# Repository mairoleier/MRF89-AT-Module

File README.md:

# MRF_AT_868/915_v1.0

This is  the first version of MRF89XA 868MHz RF module that could be controlled with AT commands. 
It has integrated MSP430FR5969 module that takes care of the control of the RF module. It stays in low power mode if there is
no data to handle.

Module web page: http://mairoleier.github.io/MRF89-AT-Module

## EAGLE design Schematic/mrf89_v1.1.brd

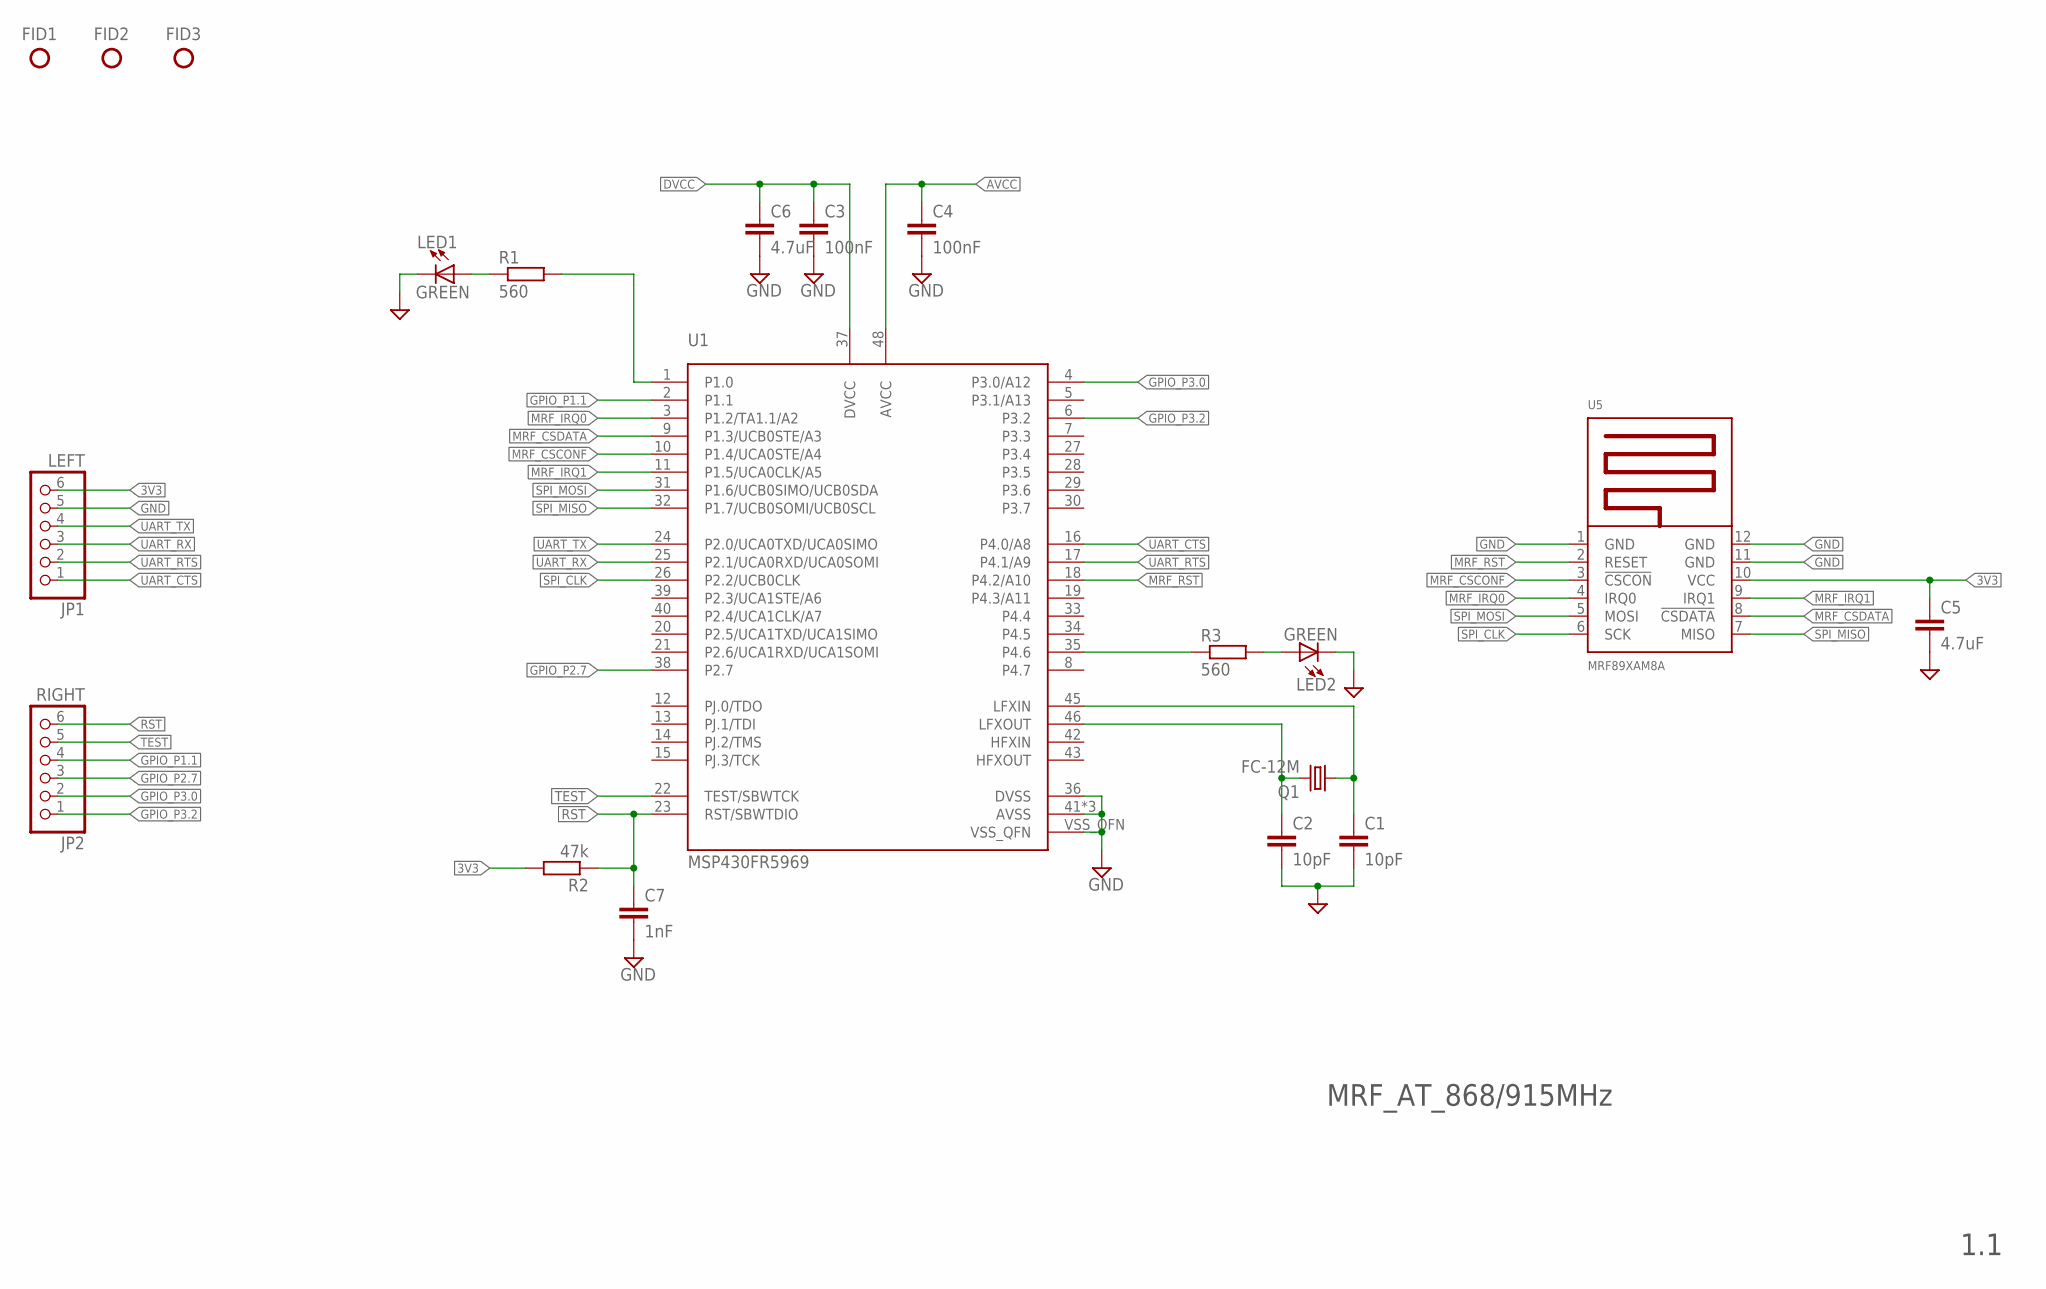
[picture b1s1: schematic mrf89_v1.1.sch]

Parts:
C1, C2: 10pF; C0603
C3, C4: 100nF; C0603
C5, C6: 4.7uF; C0603
C7: 1nF; C0603
FID1, FID2, FID3: FIDUCIAL
JP1: LEFT; 1X06
JP2: RIGHT; 1X06
LED1, LED2: GREEN; CHIP-LED0603
Q1: FC-12M
R1, R3: 560; R0603
R2: 47k; R0603
U1: MSP430FR5969; S-PVQFN-N48
U5: MRF89XAM8A; MRF89XAMXA

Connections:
3V3: C5.1, JP1.6, R2.2, U5.10 (VCC)
AVCC: C4.1, U1.48 (AVCC)
DVCC: C3.1, C6.1, U1.37 (DVCC)
GND: C1.2, C2.2, C3.2, C4.2, C5.2, C6.2, C7.2, JP1.5, LED1.C, LED2.C, U1.36 (DVSS), U1.41 (AVSS), U1.44 (AVSS), U1.47 (AVSS), U1.VSS_QFN, U5.1 (GND), U5.11 (GND), U5.12 (GND)
GPIO_P1.1: JP2.4, U1.2 (P1.1)
GPIO_P2.7: JP2.3, U1.38 (P2.7)
GPIO_P3.0: JP2.2, U1.4 (P3.0/A12)
GPIO_P3.2: JP2.1, U1.6 (P3.2)
LFXIN: C1.1, Q1.1, U1.45 (LFXIN)
LFXOUT: C2.1, Q1.2, U1.46 (LFXOUT)
MRF_!CSCONF: U1.10 (P1.4/UCA0STE/A4), U5.3 (!CSCON)
MRF_!CSDATA: U1.9 (P1.3/UCB0STE/A3), U5.8 (!CSDATA)
MRF_!RST: U1.18 (P4.2/A10), U5.2 (RESET)
MRF_IRQ0: U1.3 (P1.2/TA1.1/A2), U5.4 (IRQ0)
MRF_IRQ1: U1.11 (P1.5/UCA0CLK/A5), U5.9 (IRQ1)
unnamed: LED2.A, R3.2
unnamed: LED1.A, R1.1
P1.0: R1.2, U1.1 (P1.0)
P4.6: R3.1, U1.35 (P4.6)
RST: C7.1, JP2.6, R2.1, U1.23 (RST/SBWTDIO)
SPI_CLK: U1.26 (P2.2/UCB0CLK), U5.6 (SCK)
SPI_MISO: U1.32 (P1.7/UCB0SOMI/UCB0SCL), U5.7 (MISO)
SPI_MOSI: U1.31 (P1.6/UCB0SIMO/UCB0SDA), U5.5 (MOSI)
TEST: JP2.5, U1.22 (TEST/SBWTCK)
UART_CTS: JP1.1, U1.16 (P4.0/A8)
UART_RTS: JP1.2, U1.17 (P4.1/A9)
UART_RX: JP1.3, U1.25 (P2.1/UCA0RXD/UCA0SOMI)
UART_TX: JP1.4, U1.24 (P2.0/UCA0TXD/UCA0SIMO)

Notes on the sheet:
MRF_AT_868/915MHz
1.1

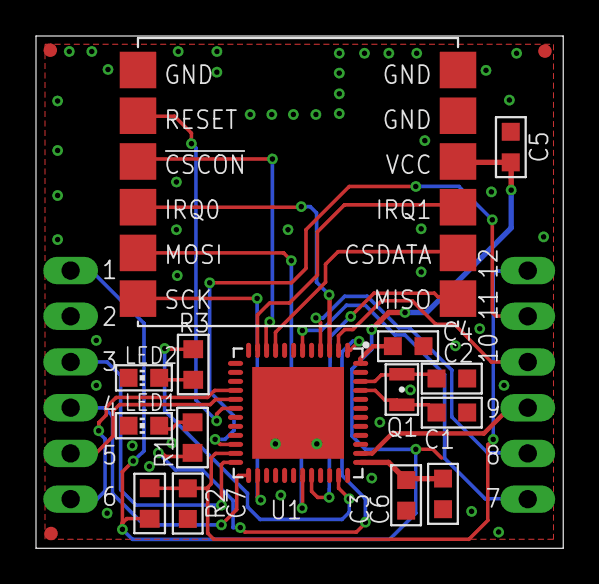
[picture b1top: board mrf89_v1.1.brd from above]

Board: 2 copper layers, 29.3 x 28.5 mm, 20 parts (0 on the bottom side), 28 nets.

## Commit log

2015-12-10 :circus_tent: Added .gitattributes & .gitignore files
2015-12-10 Test
2015-12-10 Initial schematic
2015-12-15 Schematic ready
2015-12-15 Initial working version
    Most important AT commands are working with MSP430FR5969 Launchpad
2016-01-05 Finalized version 1.0
    Finalized version of schematic and PCB.
    Version 1.0
2016-01-05 Documentation
    Added table about implemented AT commands
2016-01-05 Create gh-pages branch via GitHub
2016-01-05 Updated names
2016-01-05 Link to the module page.
2016-01-05 Link fix
2016-02-12 New board version 1.1 with bugs fixed in schematic. UART RX/TX pins were swapped. Better LED layout and 0805 caps were replaced with 0603. Software fix: MSP430 goes into LPM1. Previously LPM3 caused 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
2016-02-22 MRF_AT module picures version 1.0
